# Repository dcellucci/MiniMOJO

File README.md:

# MiniMOJO

Documentation, hardware, and software related to MiniMOJO, a robot capable of traversing a digital cellular solids lattice.

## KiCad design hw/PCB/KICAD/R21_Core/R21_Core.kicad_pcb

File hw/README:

# Hardware Notes

## MOJO Boards Rev 3

That's the one with the battery backpack.

### TeuxDeux

 1. Add solder jumper to disconnect power for I2C cable
 2. Move backpack switch to somewhere reachable
 	2a. backpack switch should turn IC on/off, IC should turn motors on/off
 3. Move servo connector up

### Notes

Pinout for ATSAM

    6 Pin | 10 Pin SAM 

    1 > 2
    2 > 1
    3 > 4
    4 > DNC 
    5 > 0
    6 > 5

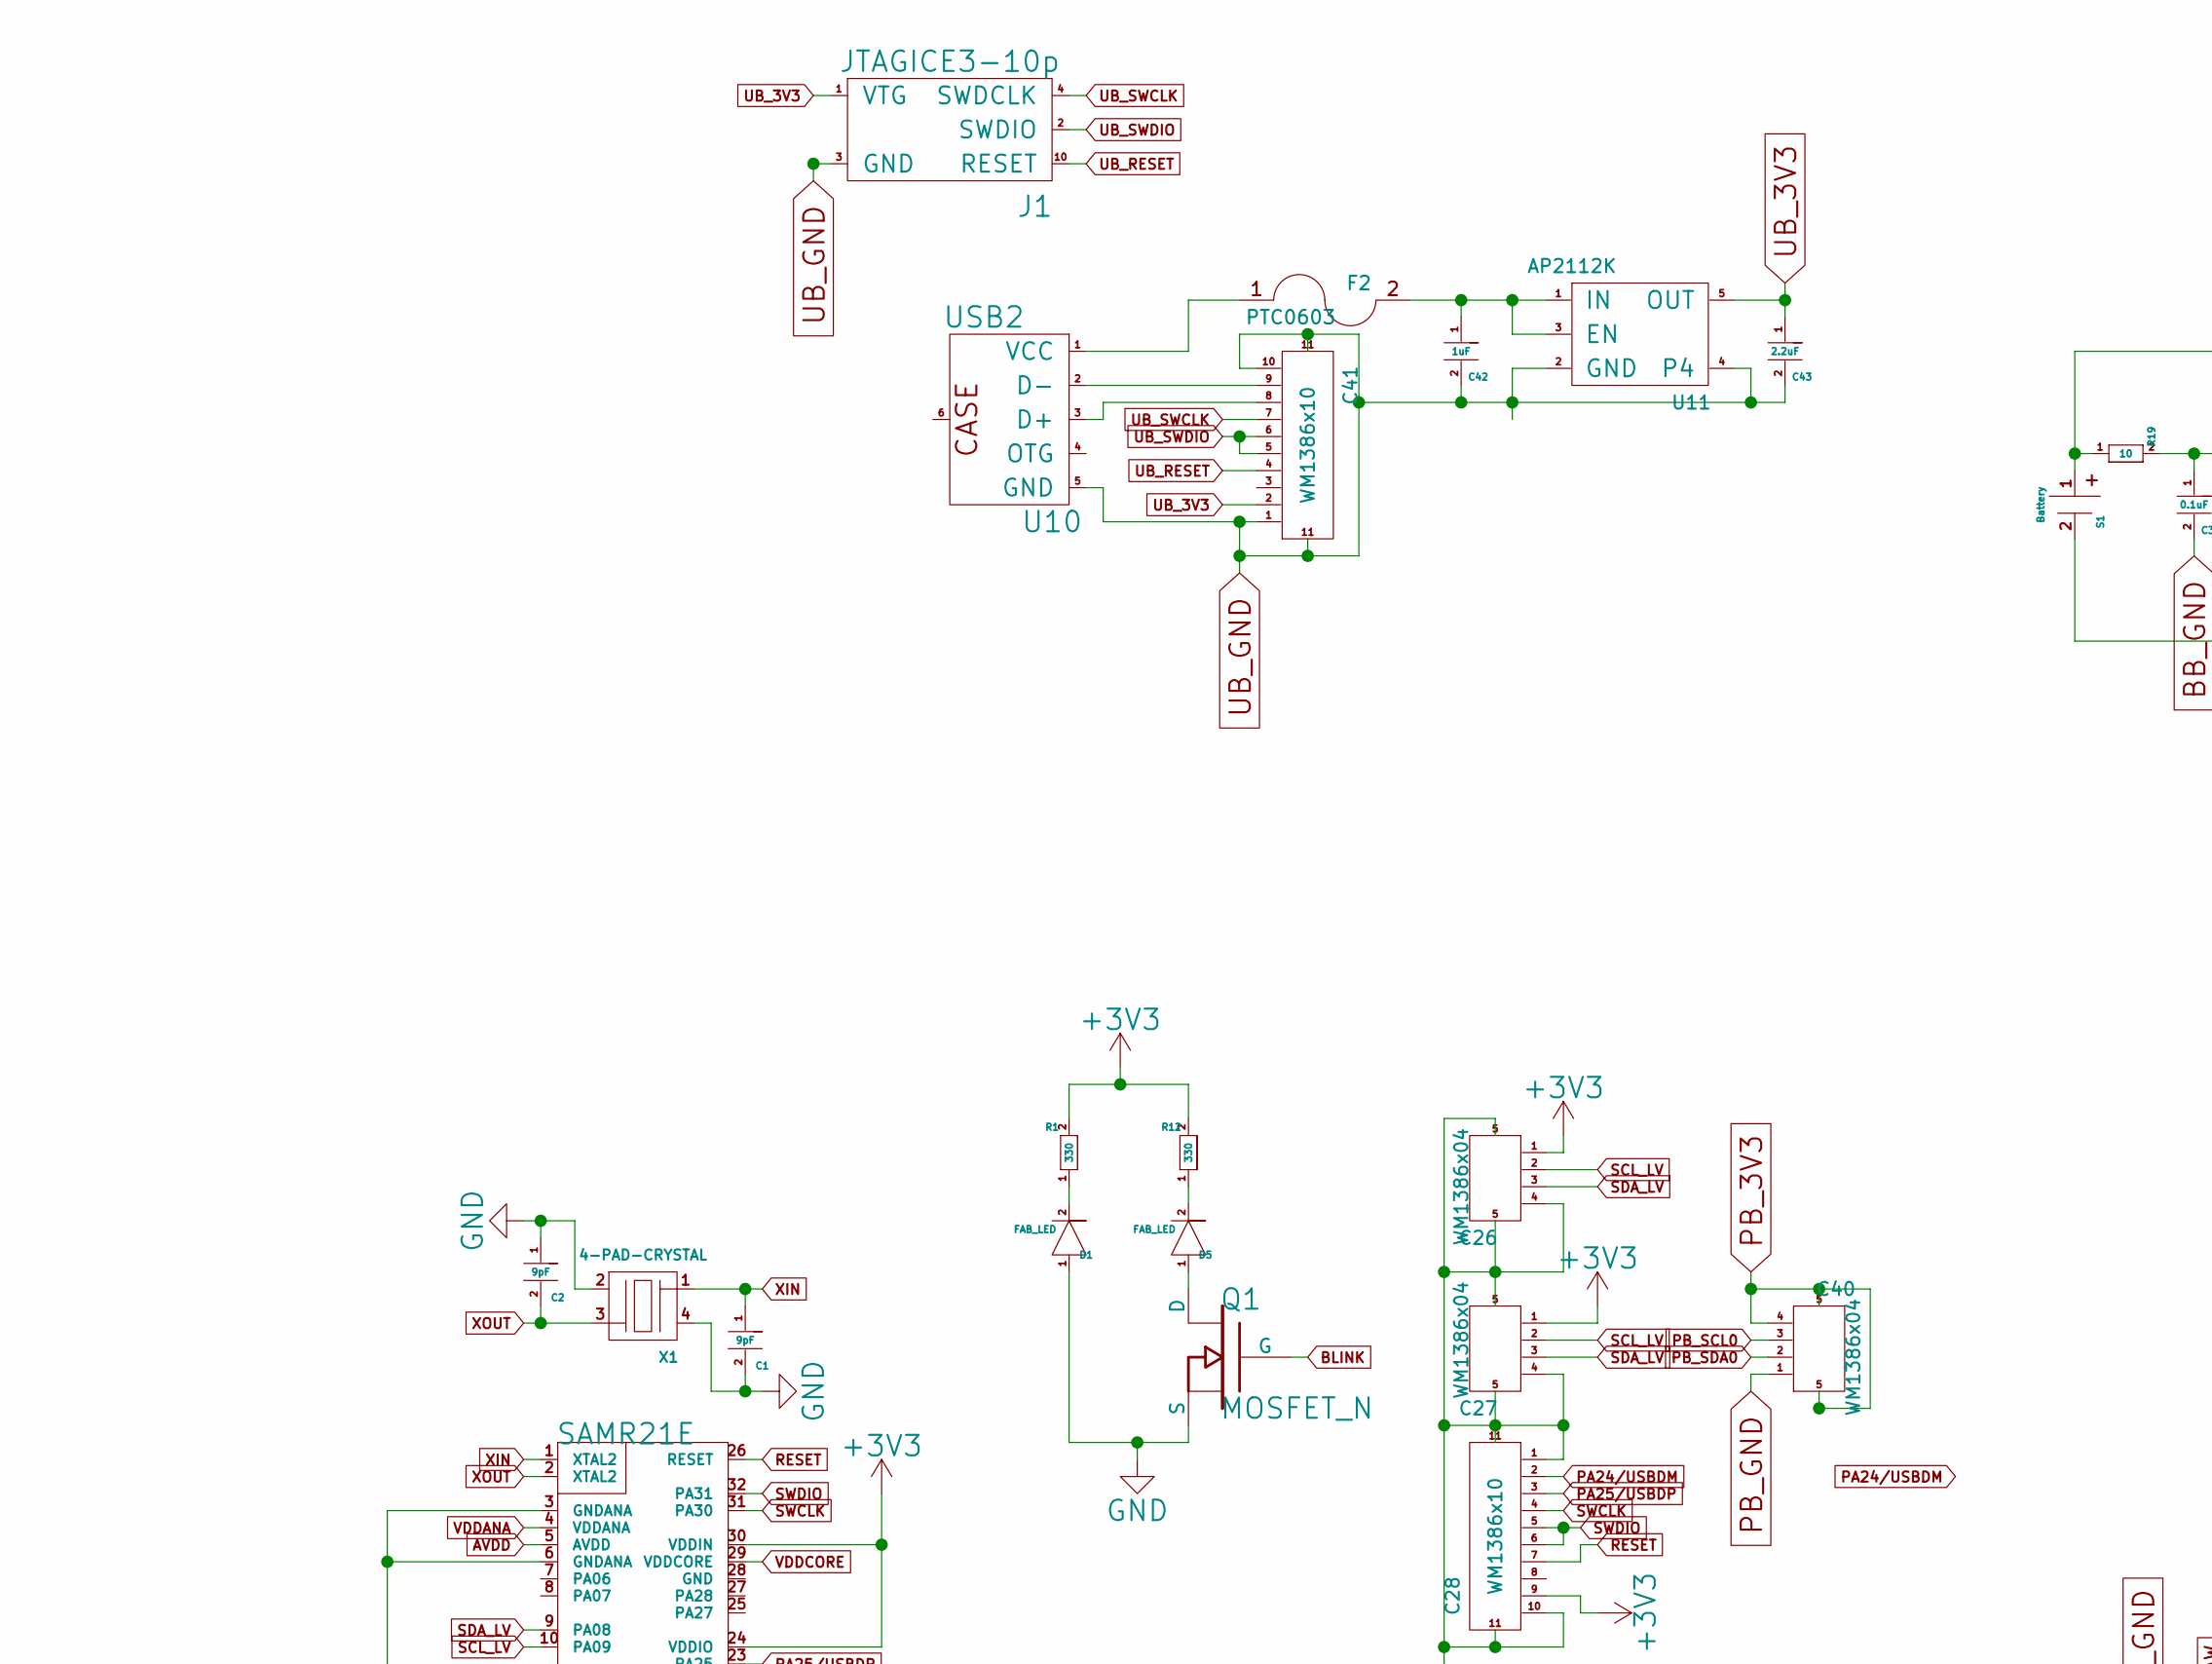
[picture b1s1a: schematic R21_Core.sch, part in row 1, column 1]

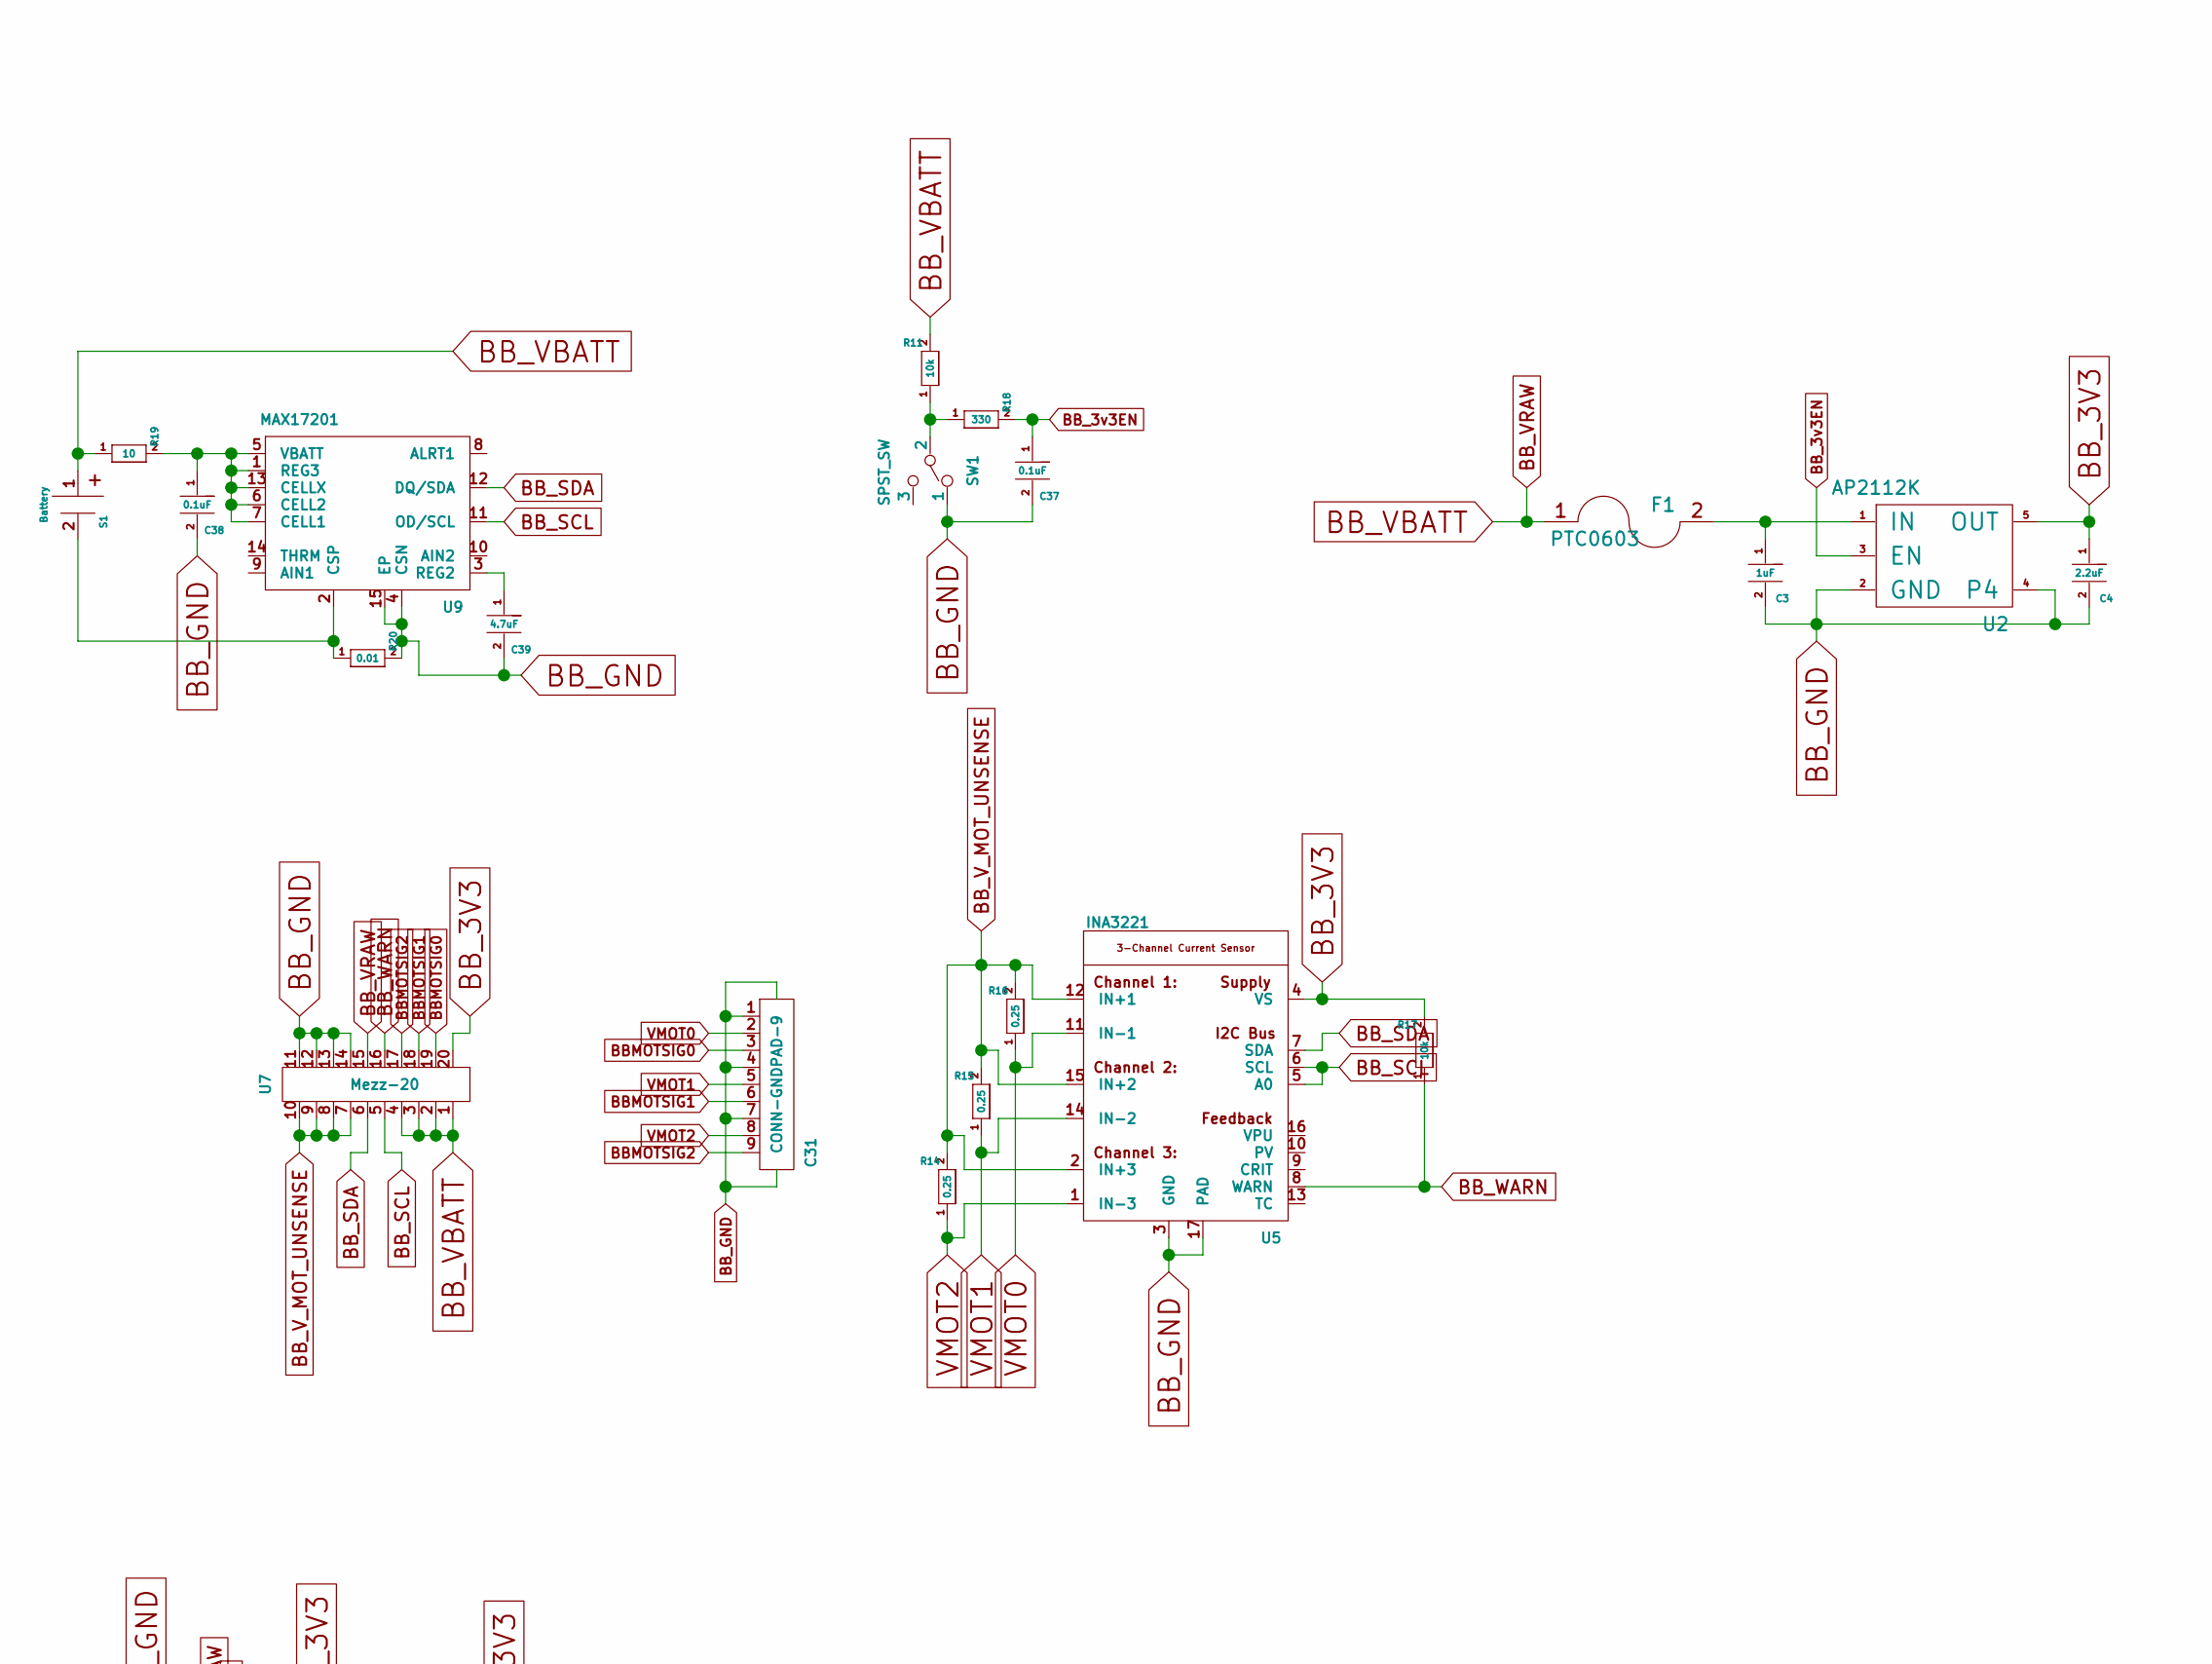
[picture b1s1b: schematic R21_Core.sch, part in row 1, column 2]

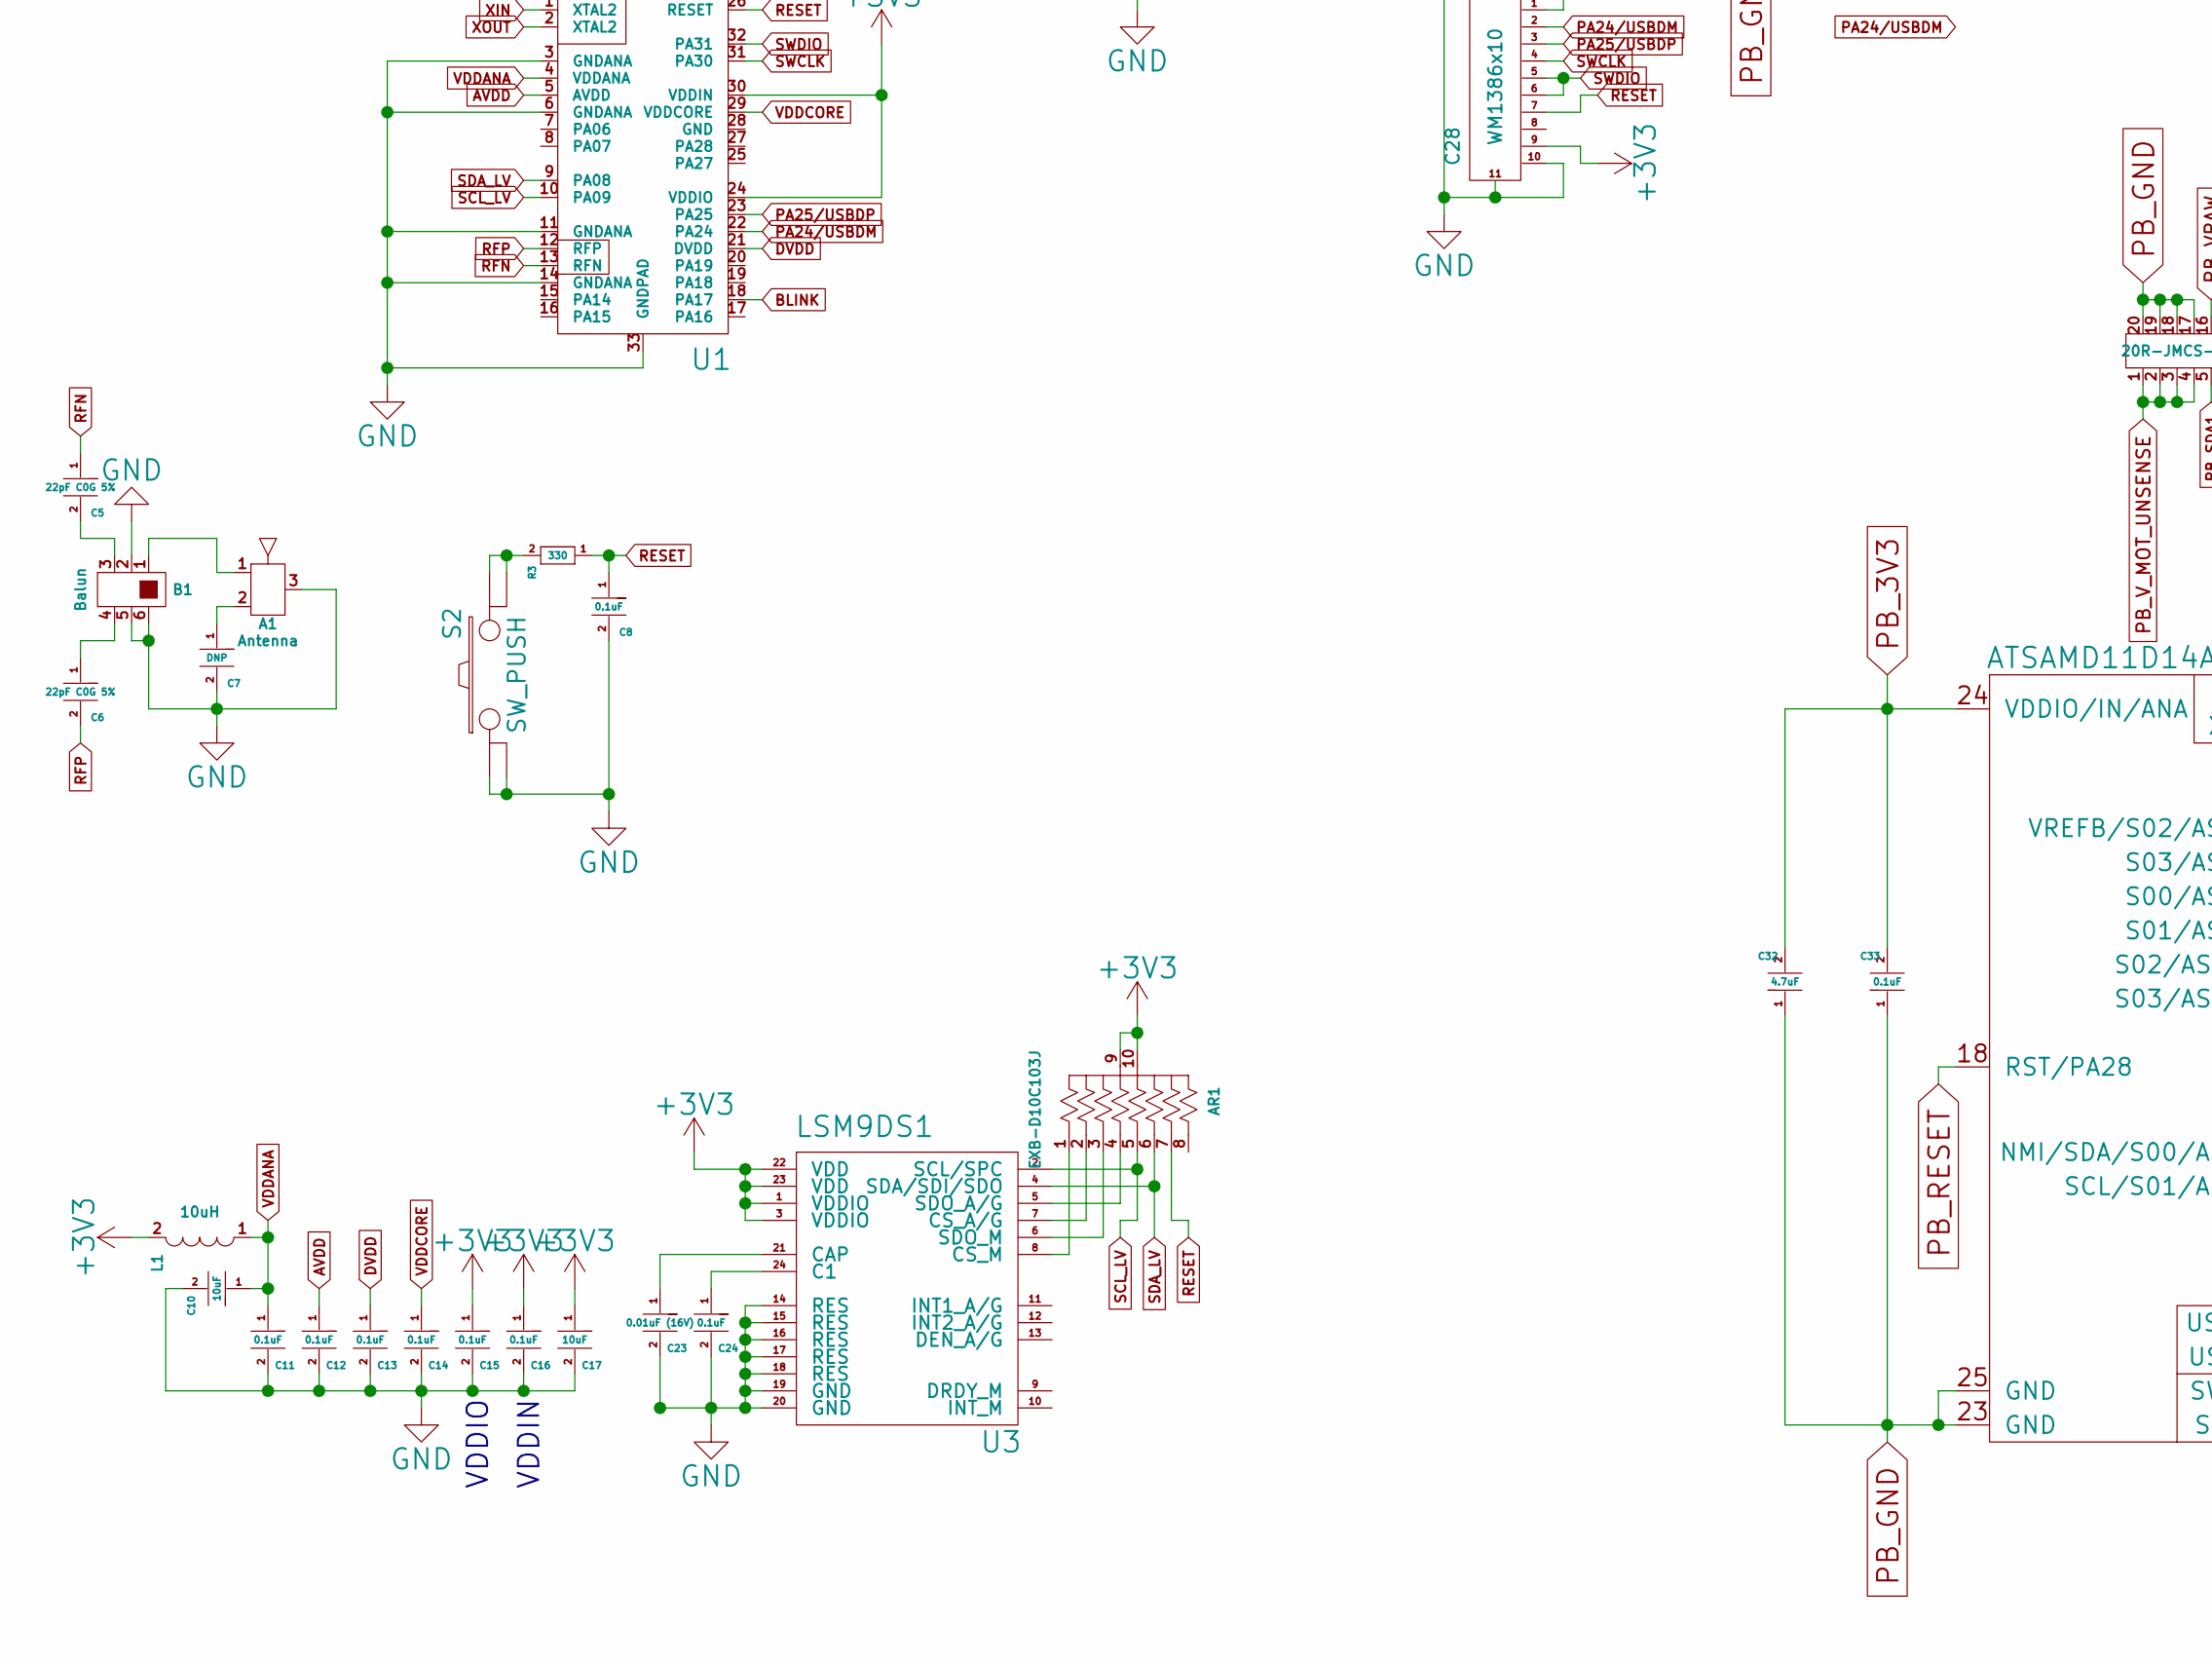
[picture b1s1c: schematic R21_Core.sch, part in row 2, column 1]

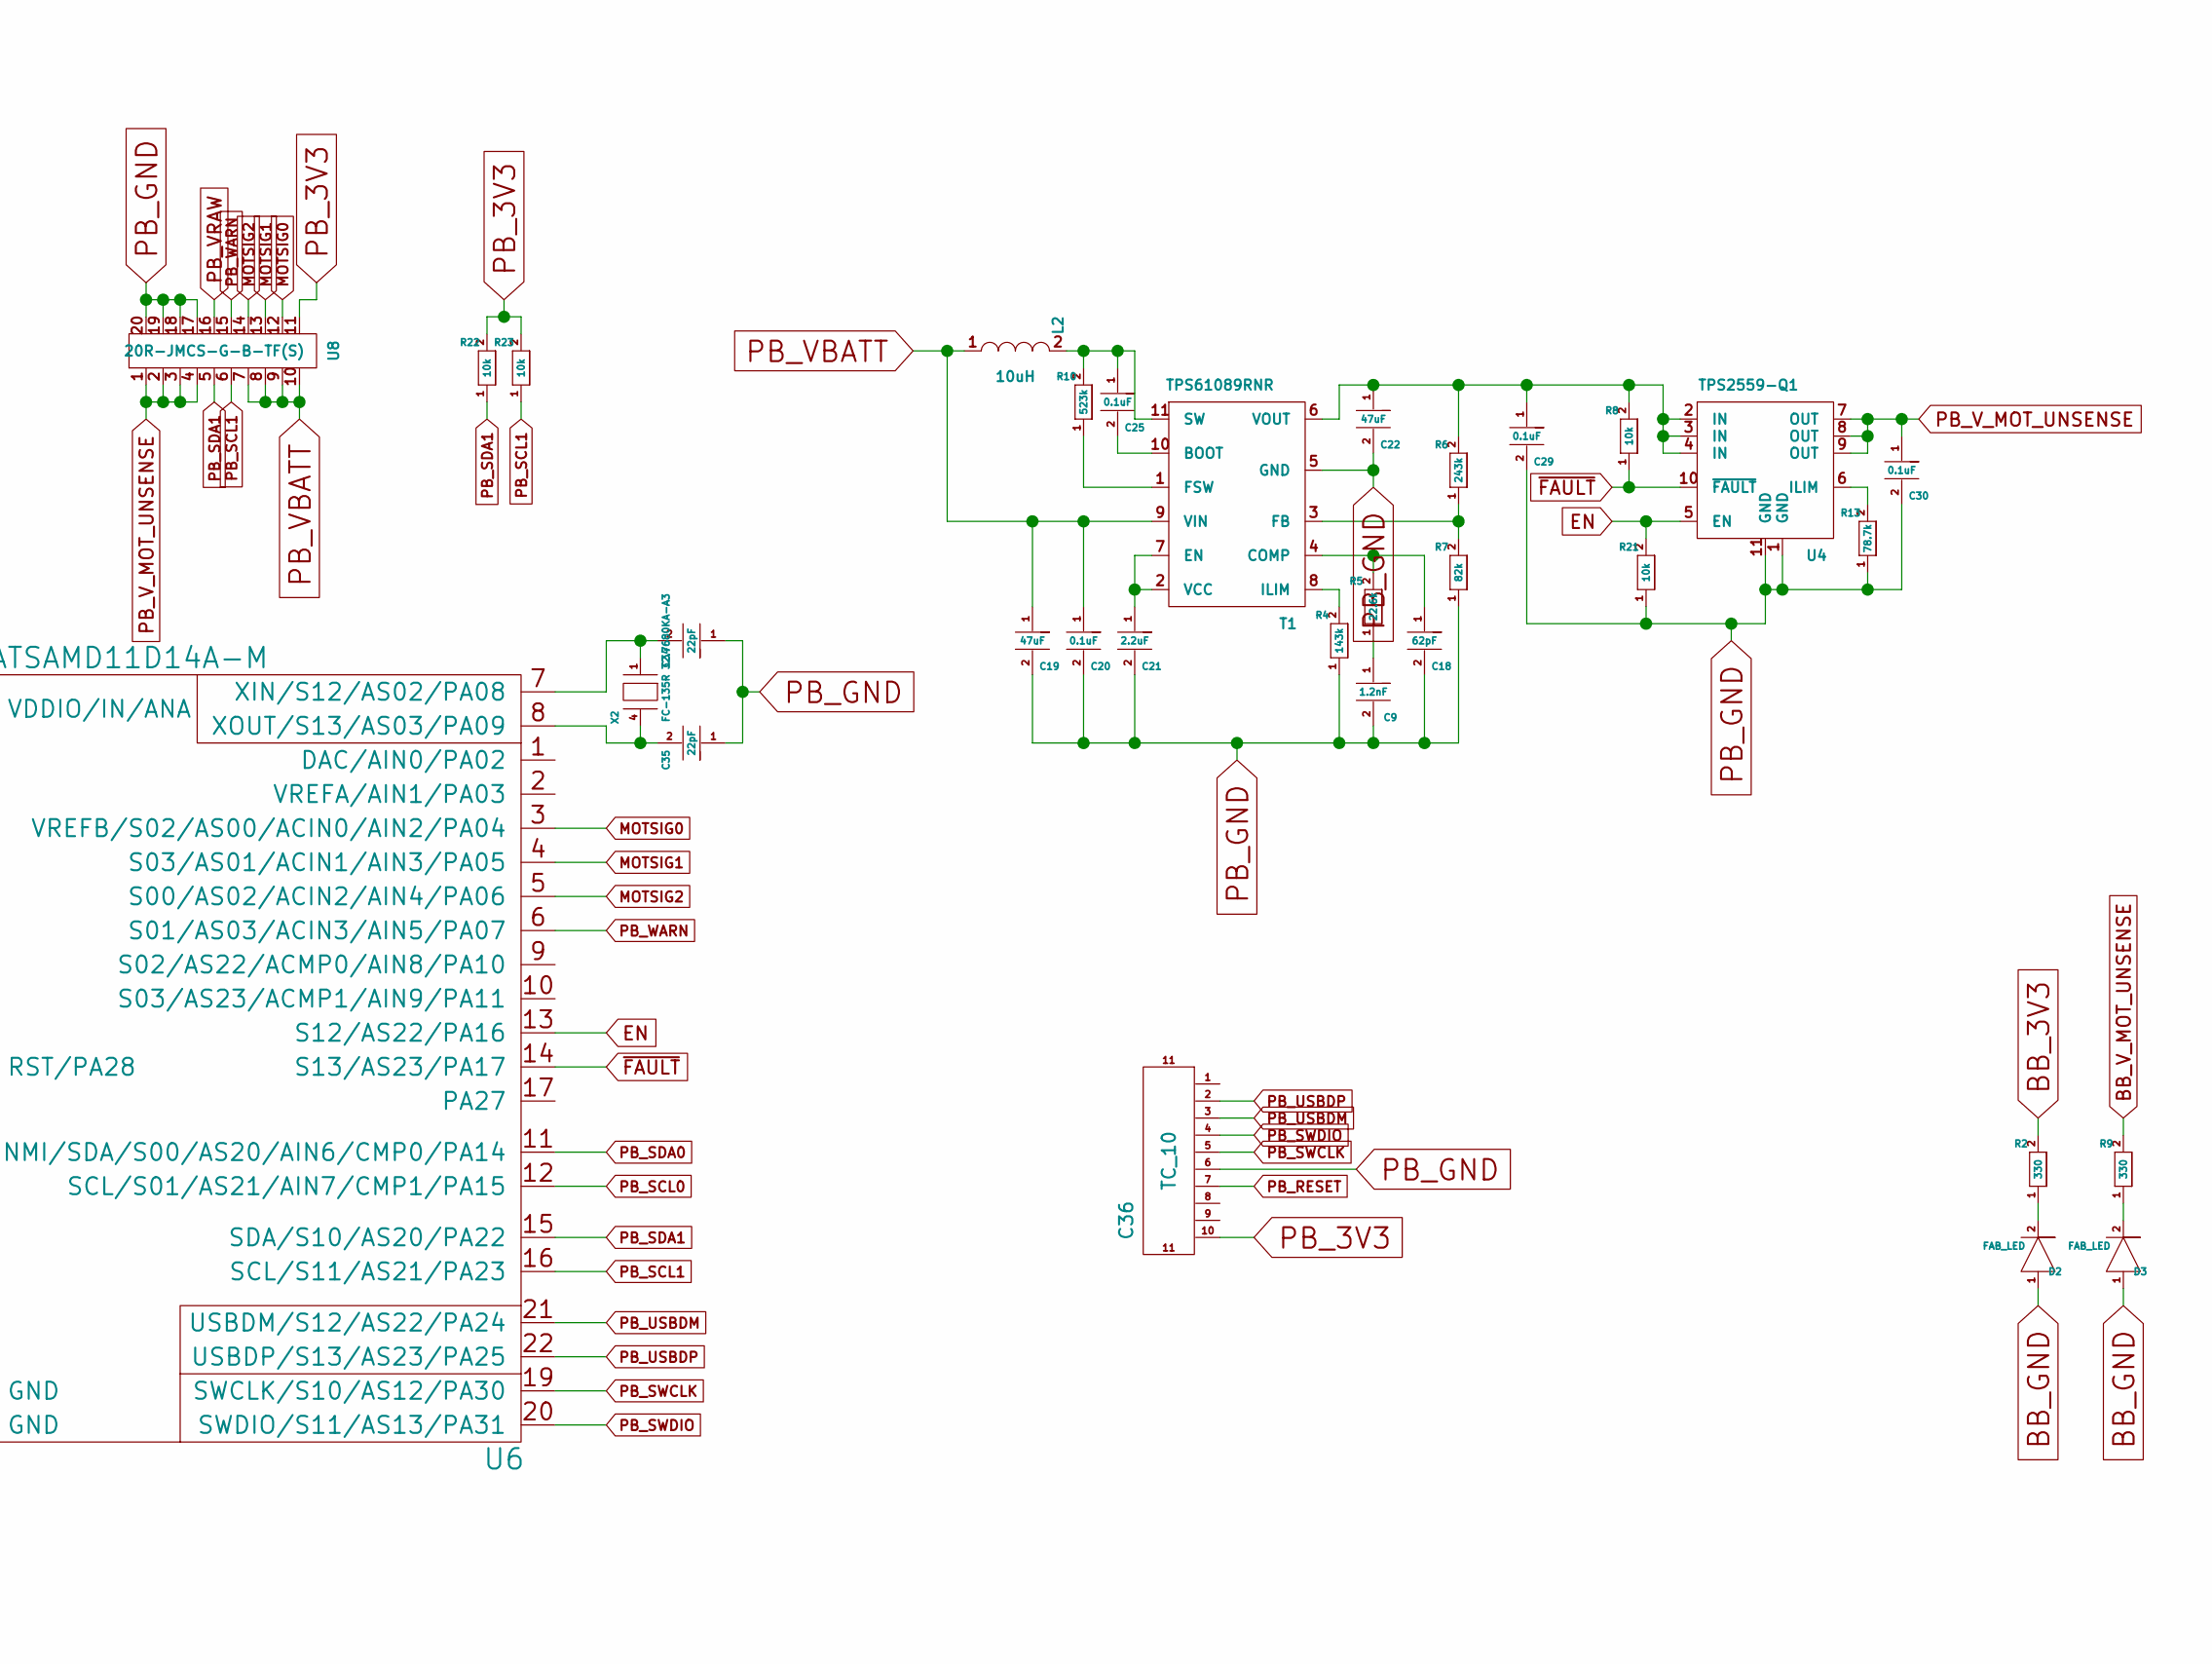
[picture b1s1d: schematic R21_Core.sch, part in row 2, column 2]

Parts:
A1: Antenna; W3008C-ANT
AR1: EXB-D10C103J; RESARR8BUS-1206
B1: Balun; 0805_Balun
C1, C2: 9pF; C_0402
C3, C42: 1uF; C_0402
C4, C43: 2.2uF; C_0402
C5, C6: 22pF C0G 5%; C_0402
C7: DNP
C8, C11, C12, C13, C14, C15, C16, C20, C24, C25, C29, C30, C33, C37, C38: 0.1uF; C_0402
C9: 1.2nF; C_0805
C10, C17: 10uF; C_0402
C18: 62pF; C_0805
C19, C22: 47uF; C_1206
C21: 2.2uF; C_0603
C23: 0.01uF (16V); C_0402
C26, C27, C40: WM1386x04; WM1386x04-REC
C28, C41: WM1386x10; WM1387x10-REC
C31: CONN-GNDPAD-9; JST-SH-9
C32, C39: 4.7uF; C_0402
C34, C35: 22pF; C_0402
C36: TC_10; TagConnectx10
D1, D2, D3, D5: FAB_LED; LED_0603
F1, F2: PTC0603; R_0603
J1: JTAGICE3-10p
L1: 10uH; C_0603
L2: 10uH; Inductor_Wurth_MAPI-4020
Q1: MOSFET_N; SOT-23
R1, R2, R3, R9, R12, R18: 330; R_0402
R4: 143k; R_1206
R5: 22.6k; R_0402
R6: 243k; R_0402
R7: 82k; R_0603
R8, R11, R17, R21, R22, R23: 10k; R_0402
R10: 523k; R_1206
R13: 78.7k; R_0402
R14, R15, R16: 0.25; R_1206
R19: 10; R_0402
R20: 0.01; R_1206
S1: Battery; Inductor_Taiyo-Yuden_NR-80xx_HandSoldering
S2: SW_PUSH; SPST-NO-TL3700
SW1: SPST_SW; SPDT-Side
T1: TPS61089RNR; TPS61089RNRR
U1: SAMR21E; QFN-32-1EP_5x5mm_Pitch0.5mm
U2, U11: AP2112K; SOT-23-5
U3: LSM9DS1
U4: TPS2559-Q1; DFN-10-1EP_3x3mm_Pitch0.5mm
U5: INA3221; QFN-16-1EP_4x4mm_Pitch0.65mm
U6: ATSAMD11D14A-M; QFN-24-1EP_4x4mm_Pitch0.5mm
U7: Mezz-20; Mezz-20-Plug
U8: 20R-JMCS-G-B-TF(S); Mezz-20-Recep
U9: MAX17201; DFN14-1EP-3x3
U10: USB2; USBMICRO-10104110
X1: 4-PAD-CRYSTAL; 4-SMD-CRYSTAL-3.2x2.5
X2: FC-135R 32.7680KA-A3; Crystal_SMD_EuroQuartz_EQ161-2pin_3.2x1.5mm

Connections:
+3V3: AR1.9, AR1.10, C15.1, C16.1, C17.1, C26.1, C27.1, C28.9, L1.2, R1.2, R12.2, U1.24 (VDDIO), U1.30 (VDDIN), U3.1 (VDDIO), U3.3 (VDDIO), U3.22 (VDD), U3.23 (VDD)
AVDD: C12.1, U1.5 (AVDD)
BBMOTSIG0: C31.3, U7.19
BBMOTSIG1: C31.6, U7.18
BBMOTSIG2: C31.9, U7.17
BB_3V3: C4.1, R2.2, R17.2, U2.5 (OUT), U5.4 (VS), U7.20
BB_3v3EN: C37.1, R18.2, U2.3 (EN)
BB_GND: C3.2, C4.2, C31.1, C31.4, C31.7, C31.10, C37.2, C38.2, C39.2, D2.1, D3.1, R20.2, SW1.1, U2.2 (GND), U2.4, U5.3 (GND), U5.17 (PAD), U7.11, U7.12, U7.13, U7.14, U9.4 (CSN), U9.15 (EP)
BB_SCL: U5.5 (A0), U5.6 (SCL), U7.5, U9.11 (OD/SCL)
BB_SDA: U5.7 (SDA), U7.6, U9.12 (DQ/SDA)
BB_VBATT: F1.1, R11.2, R19.1, S1.1, U7.1, U7.2, U7.3, U7.4, U7.15
BB_V_MOT_UNSENSE: R9.2, R14.2, R15.2, R16.2, U5.2 (IN+3), U5.12 (IN+1), U5.15 (IN+2), U7.7, U7.8, U7.9, U7.10
BB_WARN: R17.1, U5.8 (WARN), U7.16
BLINK: Q1.G, U1.18 (PA17)
DVDD: C13.1, U1.21 (DVDD)
EN: R21.2, U4.5 (EN), U6.13 (S12/AS22/PA16)
GND: A1.3, B1.2, B1.5, B1.6, C1.2, C2.1, C7.2, C8.2, C10.2, C11.2, C12.2, C13.2, C14.2, C15.2, C16.2, C17.2, C23.2, C24.2, C26.4, C26.5, C27.4, C27.5, C28.1, C28.10, C28.11, D1.1, Q1.S, S2.1, S2.2, U1.3 (GNDANA), U1.6 (GNDANA), U1.11 (GNDANA), U1.14 (GNDANA), U1.33 (GNDPAD), U3.14 (RES), U3.15 (RES), U3.16 (RES), U3.17 (RES), U3.18 (RES), U3.19 (GND), U3.20 (GND), X1.2, X1.4
MOTSIG0: U6.3 (VREFB/S02/AS00/ACIN0/AIN2/PA04), U8.12
MOTSIG1: U6.4 (S03/AS01/ACIN1/AIN3/PA05), U8.13
MOTSIG2: U6.5 (S00/AS02/ACIN2/AIN4/PA06), U8.14
unnamed: A1.1, B1.1
unnamed: A1.2, C7.1
unnamed: AR1.1, U3.8 (CS_M)
unnamed: AR1.2, U3.7 (CS_A/G)
unnamed: AR1.3, U3.6 (SDO_M)
unnamed: AR1.4, U3.5 (SDO_A/G)
unnamed: B1.3, C5.2
unnamed: B1.4, C6.1
unnamed: C3.1, F1.2, U2.1 (IN)
unnamed: C9.1, R5.1
unnamed: C18.1, R5.2, T1.4 (COMP)
unnamed: C21.1, T1.2 (VCC), T1.7 (EN)
unnamed: C22.1, C29.1, R6.2, R8.2, T1.6 (VOUT), U4.2 (IN), U4.3 (IN), U4.4 (IN)
unnamed: C23.1, U3.21 (CAP)
unnamed: C24.1, U3.24 (C1)
unnamed: C25.1, L2.2, R10.2, T1.11 (SW)
unnamed: C25.2, T1.10 (BOOT)
unnamed: C34.2, U6.7 (XIN/S12/AS02/PA08), X2.1
unnamed: C35.2, U6.8 (XOUT/S13/AS03/PA09), X2.4
unnamed: C38.1, R19.2, U9.1 (REG3), U9.5 (VBATT), U9.6 (CELL2), U9.7 (CELL1), U9.13 (CELLX)
unnamed: C39.1, U9.3 (REG2)
unnamed: C41.8, U10.3 (D+)
unnamed: C41.9, U10.2 (D-)
unnamed: C42.1, F2.2, U11.1 (IN), U11.3 (EN)
unnamed: D1.2, R1.1
unnamed: D2.2, R2.1
unnamed: D3.2, R9.1
unnamed: D5.1, Q1.D
unnamed: D5.2, R12.1
unnamed: F2.1, U10.1 (VCC)
unnamed: R3.2, S2.3, S2.4
unnamed: R4.2, T1.8 (ILIM)
unnamed: R6.1, R7.2, T1.3 (FB)
unnamed: R10.1, T1.1 (FSW)
unnamed: R11.1, R18.1, SW1.2
unnamed: R13.2, U4.6 (ILIM)
unnamed: R20.1, S1.2, U9.2 (CSP)
PA24/USBDM: C28.2, U1.22 (PA24)
PA25/USBDP: C28.3, U1.23 (PA25)
PB_3V3: C32.2, C33.2, C36.10, C40.4, C40.5, R22.2, R23.2, U6.24 (VDDIO/IN/ANA), U8.11
PB_GND: C9.2, C18.2, C19.2, C20.2, C21.2, C22.2, C29.2, C30.2, C32.1, C33.1, C34.1, C35.1, C36.6, C40.1, R4.1, R7.1, R13.1, R21.1, T1.5 (GND), U4.1 (GND), U4.11 (GND), U6.23 (GND), U6.25 (GND), U8.17, U8.18, U8.19, U8.20
PB_RESET: C36.7, U6.18 (RST/PA28)
PB_SCL0: C40.3, U6.12 (SCL/S01/AS21/AIN7/CMP1/PA15)
PB_SCL1: R23.1, U6.16 (SCL/S11/AS21/PA23), U8.6
PB_SDA0: C40.2, U6.11 (NMI/SDA/S00/AS20/AIN6/CMP0/PA14)
PB_SDA1: R22.1, U6.15 (SDA/S10/AS20/PA22), U8.5
PB_SWCLK: C36.5, U6.19 (SWCLK/S10/AS12/PA30)
PB_SWDIO: C36.4, U6.20 (SWDIO/S11/AS13/PA31)
PB_USBDM: C36.3, U6.21 (USBDM/S12/AS22/PA24)
PB_USBDP: C36.2, U6.22 (USBDP/S13/AS23/PA25)
PB_VBATT: C19.1, C20.1, L2.1, T1.9 (VIN), U8.7, U8.8, U8.9, U8.10
PB_VRAW: U8.16
PB_V_MOT_UNSENSE: C30.1, U4.7 (OUT), U4.8 (OUT), U4.9 (OUT), U8.1, U8.2, U8.3, U8.4
PB_WARN: U6.6 (S01/AS03/ACIN3/AIN5/PA07), U8.15
RESET: AR1.7, C8.1, C28.7, R3.1, U1.26 (RESET)
RFN: C5.1, U1.13 (RFN)
RFP: C6.2, U1.12 (RFP)
SCL_LV: AR1.5, C26.2, C27.2, U1.10 (PA09), U3.2 (SCL/SPC)
SDA_LV: AR1.6, C26.3, C27.3, U1.9 (PA08), U3.4 (SDA/SDI/SDO)
SWCLK: C28.4, U1.31 (PA30)
SWDIO: C28.5, C28.6, U1.32 (PA31)
UB_3V3: C41.2, C43.1, J1.1 (VTG), U11.5 (OUT)
UB_GND: C41.1, C41.10, C41.11, C42.2, C43.2, J1.3 (GND), U10.5 (GND), U11.2 (GND), U11.4
UB_RESET: C41.4, J1.10 (RESET)
UB_SWCLK: C41.7, J1.4 (SWDCLK)
UB_SWDIO: C41.5, C41.6, J1.2 (SWDIO)
VDDANA: C10.1, C11.1, L1.1, U1.4 (VDDANA)
VDDCORE: C14.1, U1.29 (VDDCORE)
VMOT0: C31.2, R16.1, U5.11 (IN-1)
VMOT1: C31.5, R15.1, U5.14 (IN-2)
VMOT2: C31.8, R14.1, U5.1 (IN-3)
XIN: C1.1, U1.1 (XTAL2), X1.1
XOUT: C2.2, U1.2 (XTAL2), X1.3
~FAULT~: R8.1, U4.10 (~FAULT), U6.14 (S13/AS23/PA17)

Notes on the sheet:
VDDIO
VDDIN

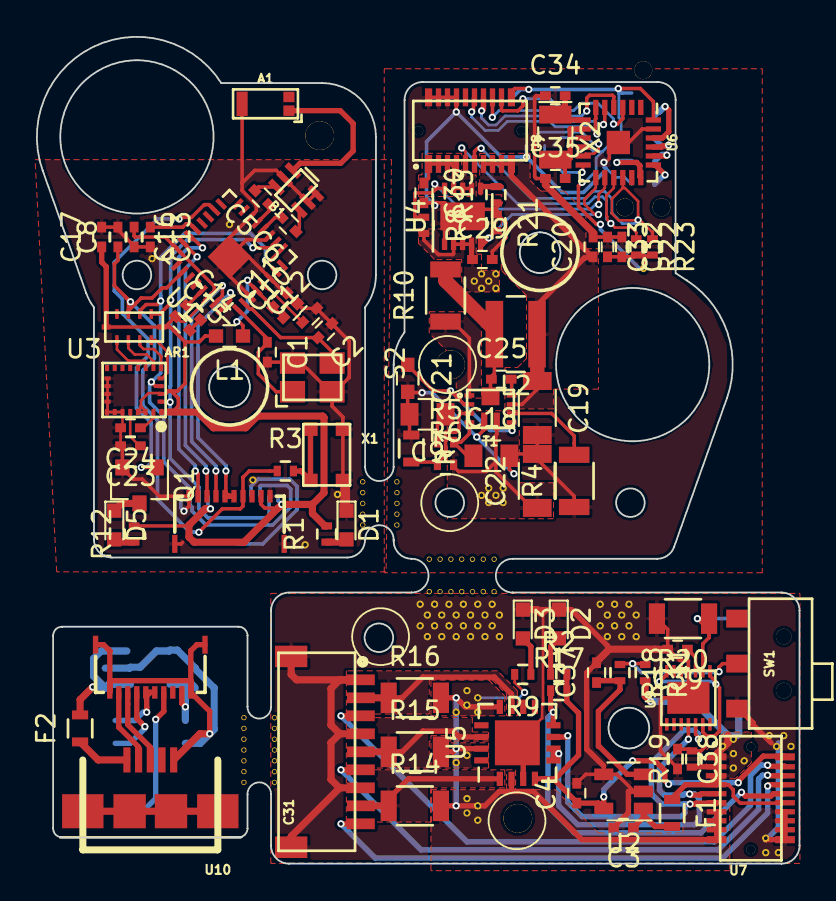
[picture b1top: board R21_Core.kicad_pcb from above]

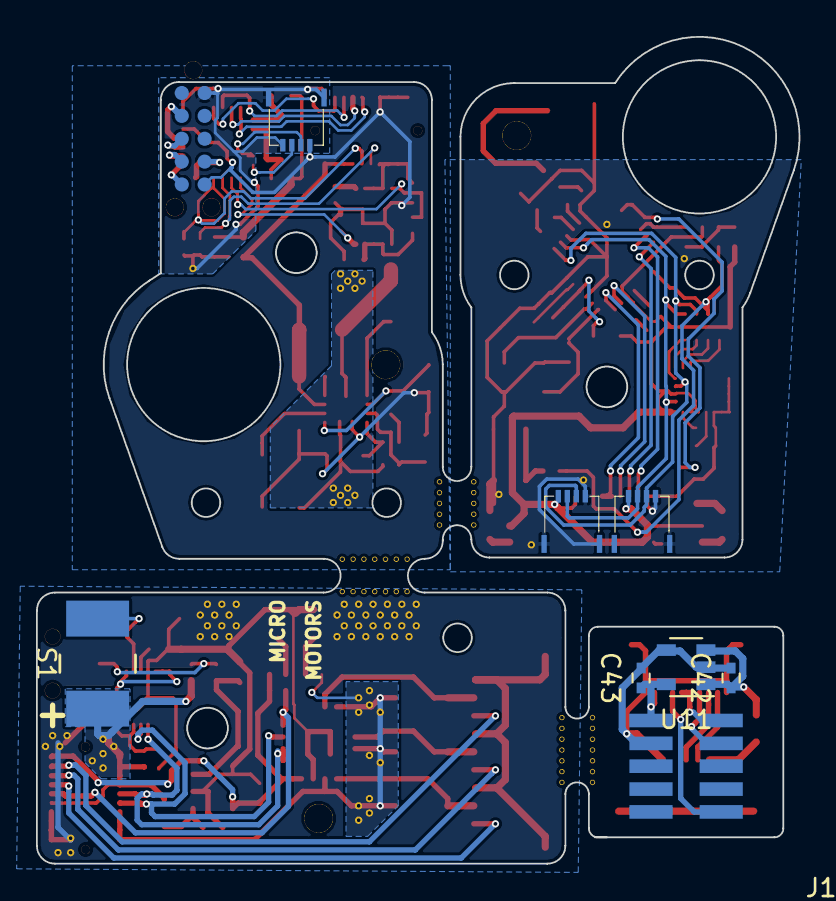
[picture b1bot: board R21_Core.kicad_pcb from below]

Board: 2 copper layers, 42.4 x 45.9 mm, 95 parts (9 on the bottom side), 92 nets.

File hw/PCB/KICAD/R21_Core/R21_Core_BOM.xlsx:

Reference Designator | Quantity | Description/Value | Manufacturer Part Number (MPN)
A1 | 1 | 2.4GHz Bluetooth, WLAN, Zigbee™ Chip RF Antenna 2.4GHz ~ 2.483GHz 2.2dBi Solder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 | W3008C
AR1 | 1 | RES ARRAY 8 RES 10K OHM 1206 | EXB-D10C103J
B1 | 1 | Balun AT86RF232 AT86RF233 ATMEGA256 | 2450BM15A0015E
C1,C2 | 2 | 9pF 50V Ceramic Capacitor C0G, NP0 0402 | GRM1555C1H9R0BA01D
C3,C42 | 2 | 1µF 6.3V Ceramic Capacitor X7R 0402 | GRM155R70J105KA12D
C4,C43 | 2 | 2.2µF 6.3V Ceramic Capacitor X5R 0402 | GRM155R60J225ME15D
C5,C6 | 2 | 22pF 50V Ceramic Capacitor C0G, NP0 0402 | C1005C0G1H220F050BA
C8,C11,C12,C13,C14,C15,C16,C20,C24,C25,C29,C30,C33,C37,C38 | 15 | 0.10µF 16V Ceramic Capacitor X7R 0402 | GRM155R71C104KA88J
C9 | 1 | CAP CER 1200PF 50V NP0 0805 | CL21C122JBFNNWE
C10,C17 | 2 | CAP CER 10UF 10V X5R 0402 | CL05A106MP5NUNC
C18 | 1 | CAP CER 62PF 50V NP0 0805 | CL21C620JBANNNC
C19,C22 | 2 | CAP CER 47UF 10V X5R 1206 | GRT31CR61A476KE13L
C21 | 1 | CAP CER 2.2UF 10V X5R 0603 | GRM188R61A225KE34D
C23 | 1 | CAP CER 10000PF 50V X7R 0402 | GRM155R71H103KA88D
C26,C27,C40 | 3 | 4 Position FFC, FPC Connector Contacts, Top and Bottom 0.020" (0.50mm) Surface 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 | 5034800400
C28,C41 | 2 | CONN FFC FPC 10POS 0.50MM R/A | 5034801000
C31 | 1 | 9 Positions Header, Shrouded Connector 0.039" (1.00mm) Surface Mount, Right Ang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 | SM09B-SRSS-TB(LF)(SN)
C32,C39 | 2 | CAP CER 4.7UF 10V X5R 0402 | CL05A475KP5NRNC
C34,C35 | 2 | 22pF 50V Ceramic Capacitor C0G, NP0 0402 | C1005C0G1H220F050BA
D1,D3 | 2 | Amber 615nm LED Indication - Discrete 2V 0603 | LA L296-Q2R2-1-Z
D2,D5 | 2 | Blue 470nm LED Indication - Discrete 3.3V 0603 | LTST-C191TBKT
F1,F2 | 2 | FUSE PTC RESET 200MA SMD 0603 | MF-FSMF020X-2
L1 | 1 | 220 Ohm Impedance Ferrite Bead 0603 (1608 Metric) Surface Mount 2A 1 Lines 50 m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 | BLM18EG221SN1D
L2 | 1 | 1.2 uH Power inductor | 74438356012
Q1 | 1 | MOSFET N-CH 60V 0.31A SOT323 | 2N7002PW,115
R1,R2,R3,R9,R12,R18 | 6 | RES SMD 330 OHM 1% 1/16W 0402 | RC0402FR-07330RL
R4 | 1 | RES SMD 143K OHM 1% 1/4W 1206 | ERJ-8ENF1433V
R5 | 1 | RES SMD 22.6K OHM 1% 1/16W 0402 | CRCW040222K6FKED
R6 | 1 | RES SMD 243K OHM 1% 1/16W 0402 | CRCW0402243KFKED
R7 | 1 | RES SMD 82K OHM 1% 1/10W 0603 | RC0603FR-0782KL
R8,R11,R17,R21,R22,R23 | 6 | RES SMD 10K OHM 1% 1/16W 0402 | CRCW040210K0FKED
R10 | 1 | RES SMD 523K OHM 1% 1/4W 1206 | ERJ-8ENF5233V
R13 | 1 | RES SMD 78.7K OHM 1% 1/10W 0402 | ERJ-2RKF7872X
R14,R15,R16 | 3 | RES SMD 0.25 OHM 1% 1/2W 1206 | CSR1206FKR250
R19 | 1 | RES SMD 10 OHM 1% 1/16W 0402 | RC0402FR-0710RL
R20 | 1 | RES SMD 0.01 OHM 1% 1W 1206 | CRF1206-FZ-R010ELF
S2 | 1 | SWITCH TACTILE SPST-NO 0.02A 15V | TL3700AF160QG
SW1 | 1 | Slide Switch SPDT Surface Mount, Right Angle | AYZ0102AGRLC
T1 | 1 | IC REG BOOST ADJ 7A SYNC 11VQFN | TPS61089RNRR
J1 | 1 | 5x2 Header JTAG 0.05" | 20021121-00010C4LF
U1 | 1 | ATSAMR21E18A IC RF TXRX+MCU ISM>1GHZ 32-VFQFN | ATSAMR21E18A-MFT
U2,U11 | 2 | IC REG LDO 3.3V 0.6A SOT25 | AP2112K-3.3TRG1
U3 | 1 | IMU ACCEL/GYRO/MAG I2C/SPI 24LGA | LSM9DS1TR
U4 | 1 | IC DISTRIBUTION SWITCH 10VSON | TPS2559QWDRCTQ1
U5 | 1 | IC CURRENT SHUNT MONITOR 16VQFN | INA3221AQRGVRQ1
U6 | 1 | IC MCU 32BIT 16KB FLASH 24QFN | ATSAMD11D14A-MNT
U7 | 1 | CONN PLUG 20POS 3MM STACK HGHT | 20P3.0-JMCS-G-TF(N)
U8 | 1 | CONN RCPT 20POS GOLD W/BOSS | 20R-JMCS-G-B-TF(S)
U9 | 1 | IC BATTERY MONITOR 14TDFN | MAX17201G+
U10 | 1 | USB - micro B USB 2.0 Receptacle Connector 5 Position Surface Mount, Right Angl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 | 10104110-0001LF
X1 | 1 | CRYSTAL 16.0000MHZ 10PF SMD | ABM8-16.000MHZ-10-1-U-T
X2 | 1 | CRYSTAL 32.7680KHZ 12.5PF SMT | FC-135R 32.7680KF-A3
 | 93
